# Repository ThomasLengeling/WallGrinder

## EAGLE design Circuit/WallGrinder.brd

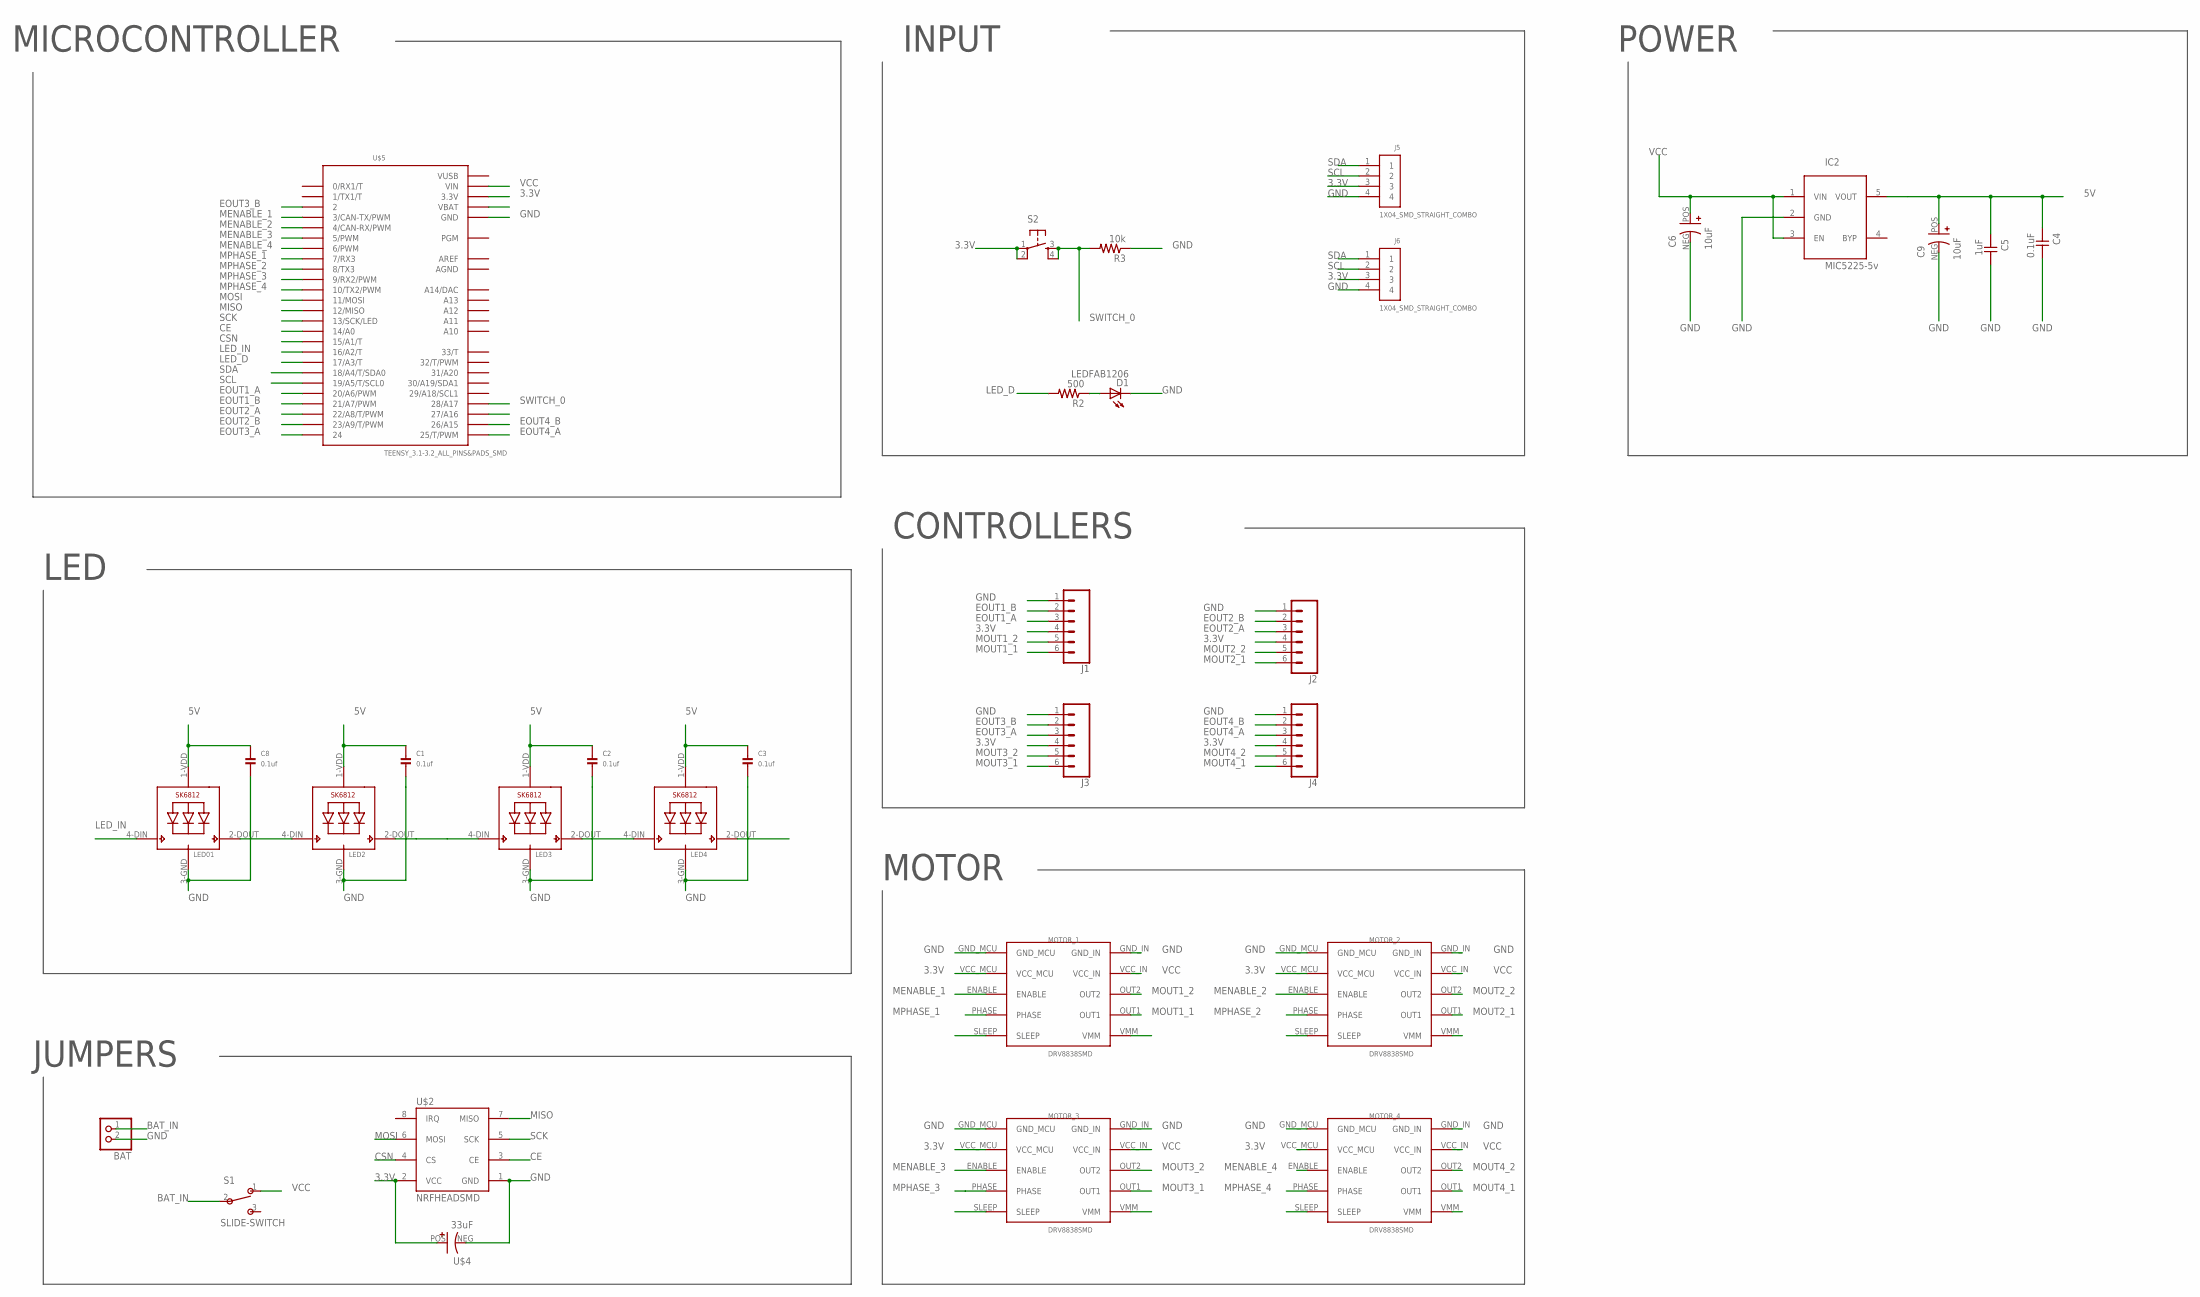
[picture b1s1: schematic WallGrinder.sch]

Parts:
BAT: JST_2PIN-SMT-RA; JST-PH-2-SMT-RA
C1, C2, C3, C8: 0.1uf; 1206
C4: 0.1uF; C1206FAB
C5: 1uF; C1206FAB
C6, C9: 10uF; PANASONIC-CAP-SMD-B
D1: LEDFAB1206; LED1206FAB
IC2: MIC5225-5v; SOT23-5L
J1, J2, J3, J4: CONN_06SMD_MALE; 1X06_SMD_MALE
J5, J6: 1X04_SMD_STRAIGHT_COMBO; 1X4-SMT
LED01, LED2, LED3, LED4: SK6812_5050; LED5050
MOTOR_1, MOTOR_2, MOTOR_3, MOTOR_4: DRV8838SMD
R2: 500; R1206FAB
R3: 10k; R1206FAB
S1: SLIDE-SWITCH; AYZ0102AGRLC
S2: 6MM_SWITCH6MM_SWITCH; 6MM_SWITCH
U$2: NRFHEADSMD; 2.54MM
U$4: 33uF; PANASONIC-CAP-SMD-C
U$5: TEENSY_3.1-3.2_ALL_PINS&PADS_SMD; TEENSY_3.0-3.2_ALL_PINS_&_PADS_SMD

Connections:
3.3V: J1.4, J2.4, J3.4, J4.4, J5.3, J6.3, MOTOR_1.VCC_MCU, MOTOR_2.VCC_MCU, MOTOR_3.VCC_MCU, MOTOR_4.VCC_MCU, S2.1, S2.2 (P1), U$2.2 (VCC), U$4.POS (+), U$5.3.3V, U$5.3.3V1 (3.3V), U$5.3.3V2 (3.3V)
5V: C1.1, C2.1, C3.1, C4.1, C5.1, C8.1, C9.POS (+), IC2.5 (VOUT), LED01.1-VDD (VDD), LED2.1-VDD (VDD), LED3.1-VDD (VDD), LED4.1-VDD (VDD)
AGND: U$5.AGND
AREF: U$5.AREF
BAT_IN: BAT.1 (2), S1.2
CE: U$2.3 (CE), U$5.14/A0
CSN: U$2.4 (CS), U$5.15/A1 (15/A1/T)
EOUT1_A: J1.3, U$5.20/A6 (20/A6/PWM)
EOUT1_B: J1.2, U$5.21/A7 (21/A7/PWM)
EOUT2_A: J2.3, U$5.22/A8 (22/A8/T/PWM)
EOUT2_B: J2.2, U$5.23/A9 (23/A9/T/PWM)
EOUT3_A: J3.3, U$5.24
EOUT3_B: J3.2, U$5.2
EOUT4_A: J4.3, U$5.25 (25/T/PWM)
EOUT4_B: J4.2, U$5.26 (26/A15)
GND: BAT.2 (1), C1.2, C2.2, C3.2, C4.2, C5.2, C6.NEG (-), C8.2, C9.NEG (-), D1.2 (C), IC2.2 (GND), J1.1, J2.1, J3.1, J4.1, J5.4, J6.4, LED01.3-GND (GND), LED2.3-GND (GND), LED3.3-GND (GND), LED4.3-GND (GND), MOTOR_1.GND_IN, MOTOR_1.GND_MCU, MOTOR_2.GND_IN, MOTOR_2.GND_MCU, MOTOR_3.GND_IN, MOTOR_3.GND_MCU, MOTOR_4.GND_IN, MOTOR_4.GND_MCU, R3.1, U$2.1 (GND), U$4.NEG (-), U$5.GND, U$5.GND1 (GND), U$5.GND2 (GND)
LED_D: R2.2, U$5.17/A3 (17/A3/T)
LED_IN: LED01.4-DIN (DI), U$5.16/A2 (16/A2/T)
LED_IN1: LED2.2-DOUT (DO), LED3.4-DIN (DI)
LED_IN2: LED3.2-DOUT (DO), LED4.4-DIN (DI)
MENABLE_1: MOTOR_1.ENABLE, U$5.3 (3/CAN-TX/PWM)
MENABLE_2: MOTOR_2.ENABLE, U$5.4 (4/CAN-RX/PWM)
MENABLE_3: MOTOR_3.ENABLE, U$5.5 (5/PWM)
MENABLE_4: MOTOR_4.ENABLE, U$5.6 (6/PWM)
MISO: U$2.7 (MISO), U$5.12 (12/MISO)
MOSI: U$2.6 (MOSI), U$5.11 (11/MOSI)
MOUT1_1: J1.6, MOTOR_1.OUT1
MOUT1_2: J1.5, MOTOR_1.OUT2
MOUT2_1: J2.6, MOTOR_2.OUT1
MOUT2_2: J2.5, MOTOR_2.OUT2
MOUT3_1: J3.6, MOTOR_3.OUT1
MOUT3_2: J3.5, MOTOR_3.OUT2
MOUT4_1: J4.6, MOTOR_4.OUT1
MOUT4_2: J4.5, MOTOR_4.OUT2
MPHASE_1: MOTOR_1.PHASE, U$5.7 (7/RX3)
MPHASE_2: MOTOR_2.PHASE, U$5.8 (8/TX3)
MPHASE_3: MOTOR_3.PHASE, U$5.9 (9/RX2/PWM)
MPHASE_4: MOTOR_4.PHASE, U$5.10 (10/TX2/PWM)
unnamed: D1.1 (A), R2.1
unnamed: LED01.2-DOUT (DO), LED2.4-DIN (DI)
SCK: U$2.5 (SCK), U$5.13 (13/SCK/LED)
SCL: J5.2, J6.2, U$5.19/A5 (19/A5/T/SCL0)
SDA: J5.1, J6.1, U$5.18/A4 (18/A4/T/SDA0)
SWITCH_0: R3.2, S2.3 (S), S2.4 (S1), U$5.28 (28/A17)
VCC: C6.POS (+), IC2.1 (VIN), IC2.3 (EN), MOTOR_1.VCC_IN, MOTOR_2.VCC_IN, MOTOR_3.VCC_IN, MOTOR_4.VCC_IN, S1.1, U$5.VIN
VUSB: U$5.VUSB

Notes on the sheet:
JUMPERS
MICROCONTROLLER
INPUT
CONTROLLERS
MOTOR
LED
POWER

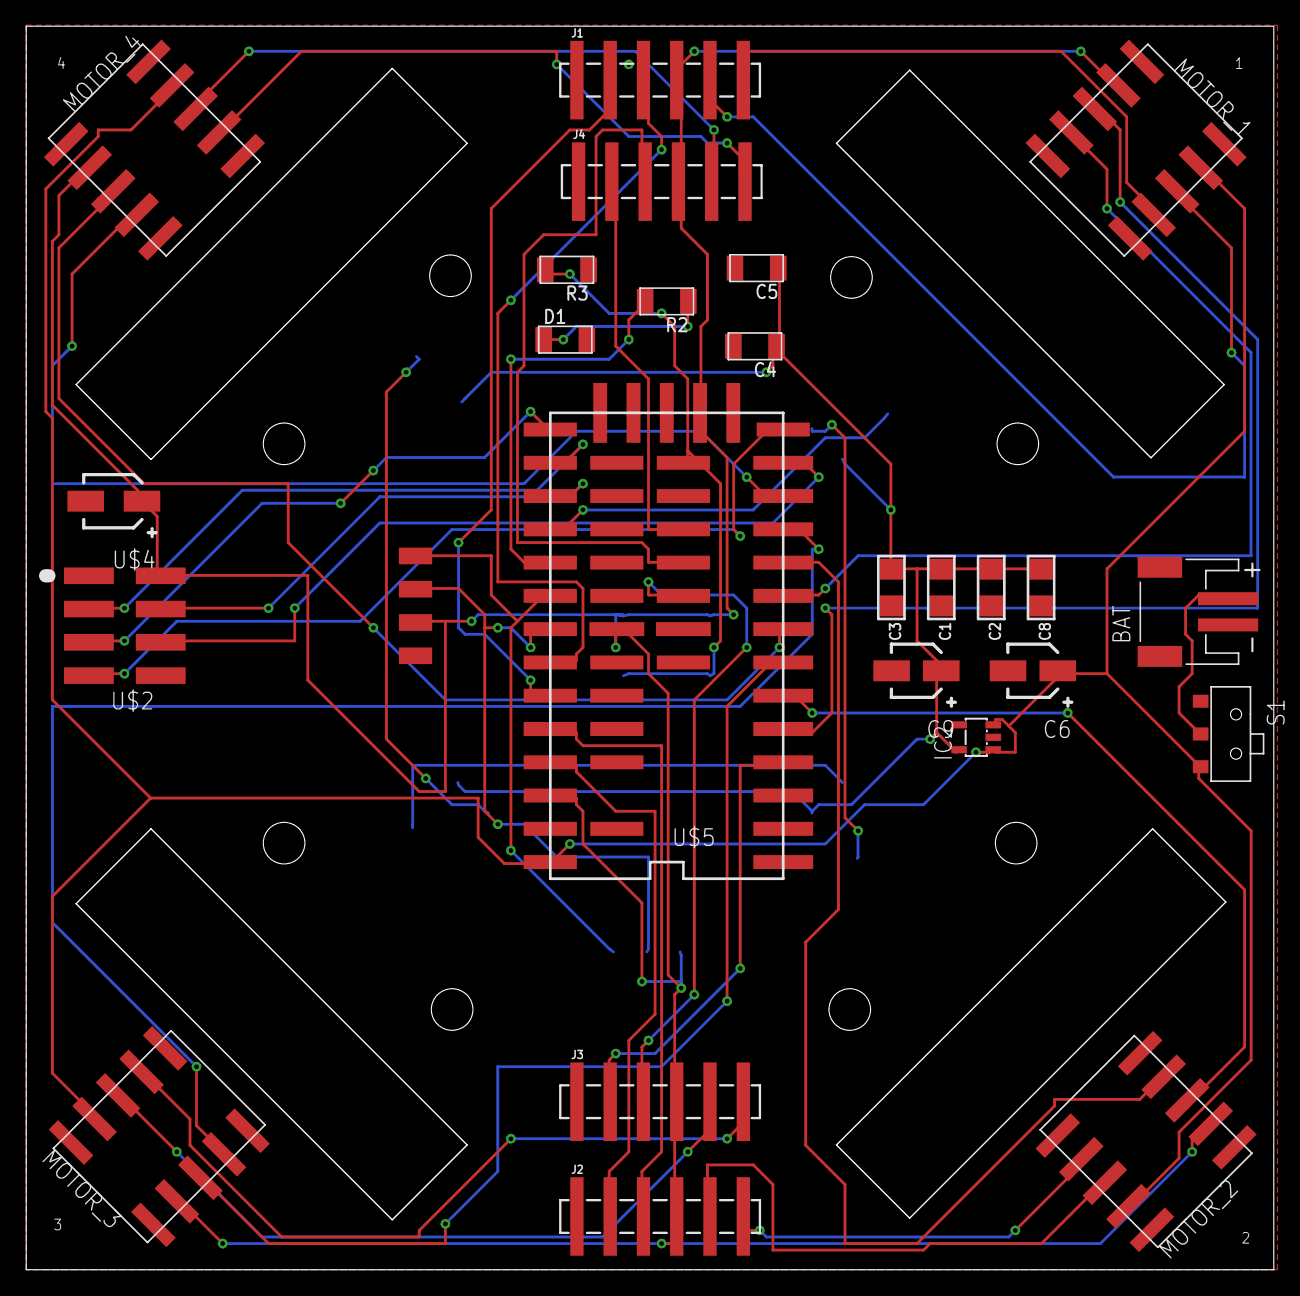
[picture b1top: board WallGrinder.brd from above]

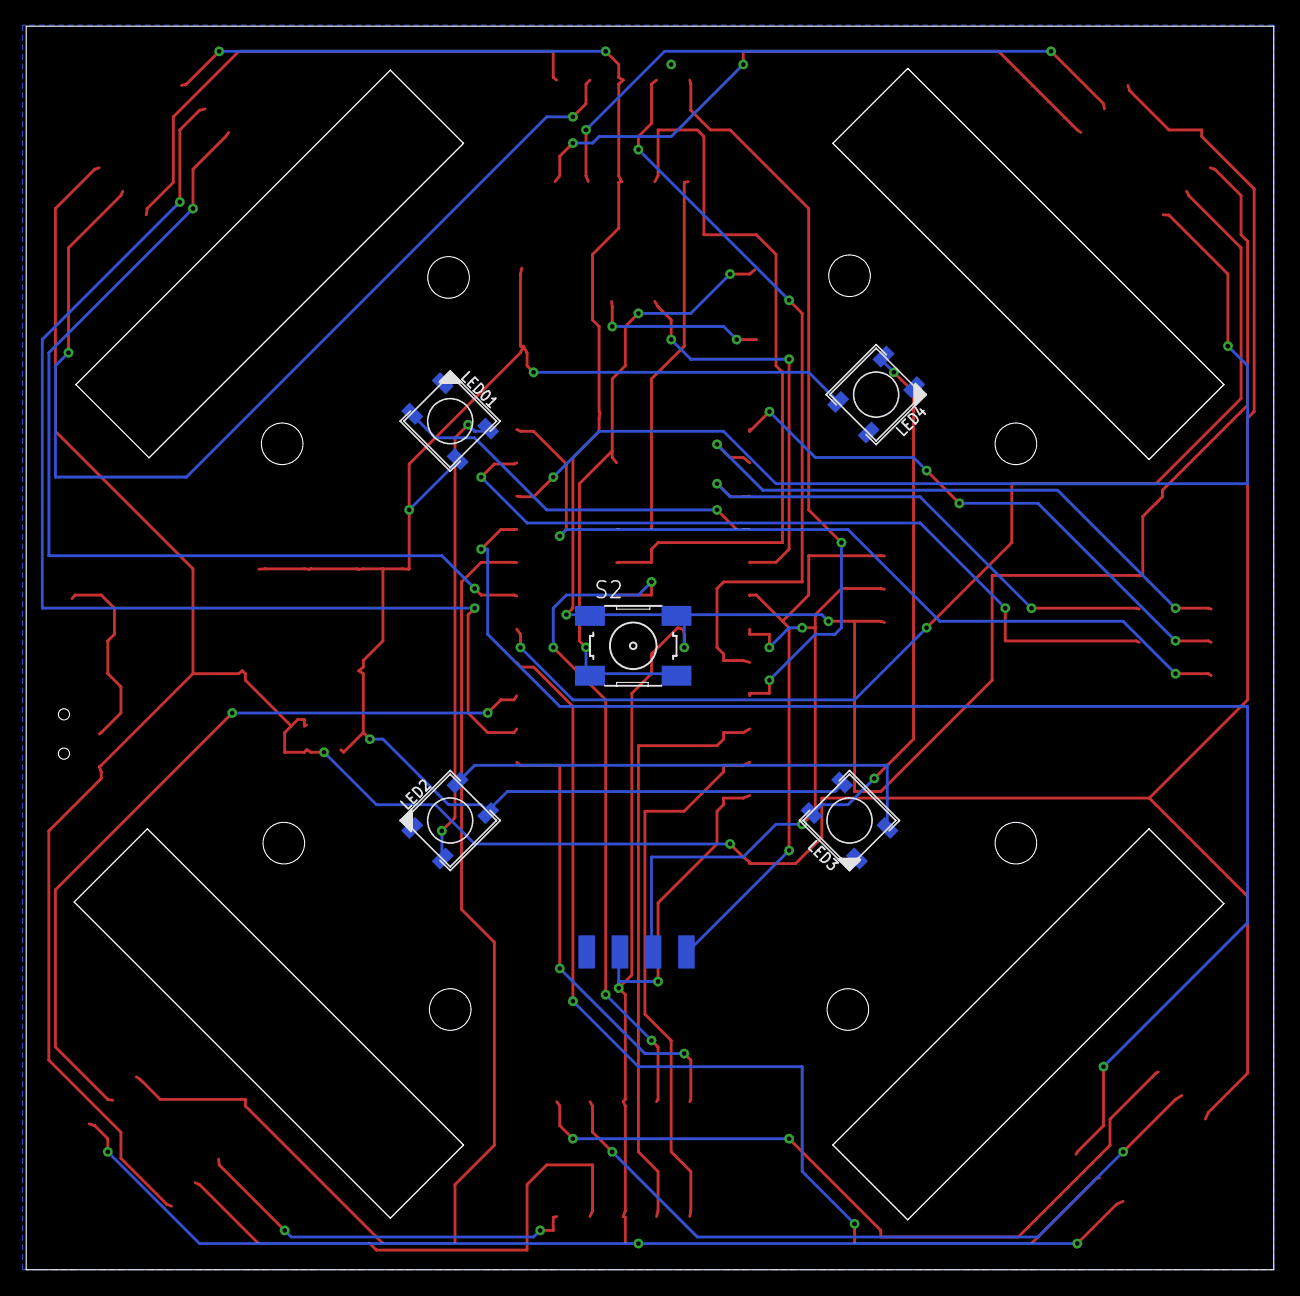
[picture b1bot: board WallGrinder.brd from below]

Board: 2 copper layers, 95.1 x 94.8 mm, 32 parts (6 on the bottom side), 43 nets.

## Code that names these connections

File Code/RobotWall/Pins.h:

//define SWITCH
#define SWITCH       A17

//LED NEOPIXEL
#define LED_NEO      16

#define NUMPIXELS     4

//LED DEBUG
#define LED_DEBUG    17

//Motor 1
#define MENABLE_1     3
#define MPHASE_1      7
#define EOUT1_A       20
#define EOUT1_B       21

//Motor 2
#define MENABLE_2     4
#define MPHASE_2      8
#define EOUT2_A       22
#define EOUT2_B       23

//Motor 3
#define MENABLE_3     5
#define MPHASE_3      9
#define EOUT3_A       24
#define EOUT3_B       2

//Motor 4
#define MENABLE_4     6
#define MPHASE_4      10
#define EOUT4_A       25
#define EOUT4_B       26

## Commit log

2019-08-23 readmd
2019-09-04 circuit
2019-11-04 motor encoder
2019-11-05 enconders
2020-01-08 movement

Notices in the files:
parts and their libraries:
microbuilder: This work is placed in the public domain, and may be freely used for commercial and non-commercial work with the following conditions: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
SparkFun-Connectors: Licensing: Creative Commons ShareAlike 4.0 International - https://creativecommons.org/licenses/by-sa/4.0
